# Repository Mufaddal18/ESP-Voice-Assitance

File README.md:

# ESP-Voice-Assitance

🚀 Excited to share my latest project: a fully integrated PCB for a voice assistant inspired by Avi Patel’s Gemini Voice Assistant!

This innovative design utilizes the Deepgram API for seamless speech-to-text conversion and leverages the Gemini API for intelligent responses, all while harnessing Google Text-to-Speech for natural-sounding replies.

🔑 Key Features:

1. Integrated Components: Powered by the ESP32, featuring a USB to TTL circuit, I2S microphone, and robust amplifier for top-notch performance.

2. Speech-to-Text Conversion: Impressively quick response time with Deepgram API.

3. Smart Audio Switching: Automatically toggles between speaker and earphone output for a personalized listening experience.

4. WAV File Storage: Efficiently processes longer questions by storing them as WAV files on an SD card.

5. Replay Functionality: A dedicated button to replay the last response, enhancing user interaction.

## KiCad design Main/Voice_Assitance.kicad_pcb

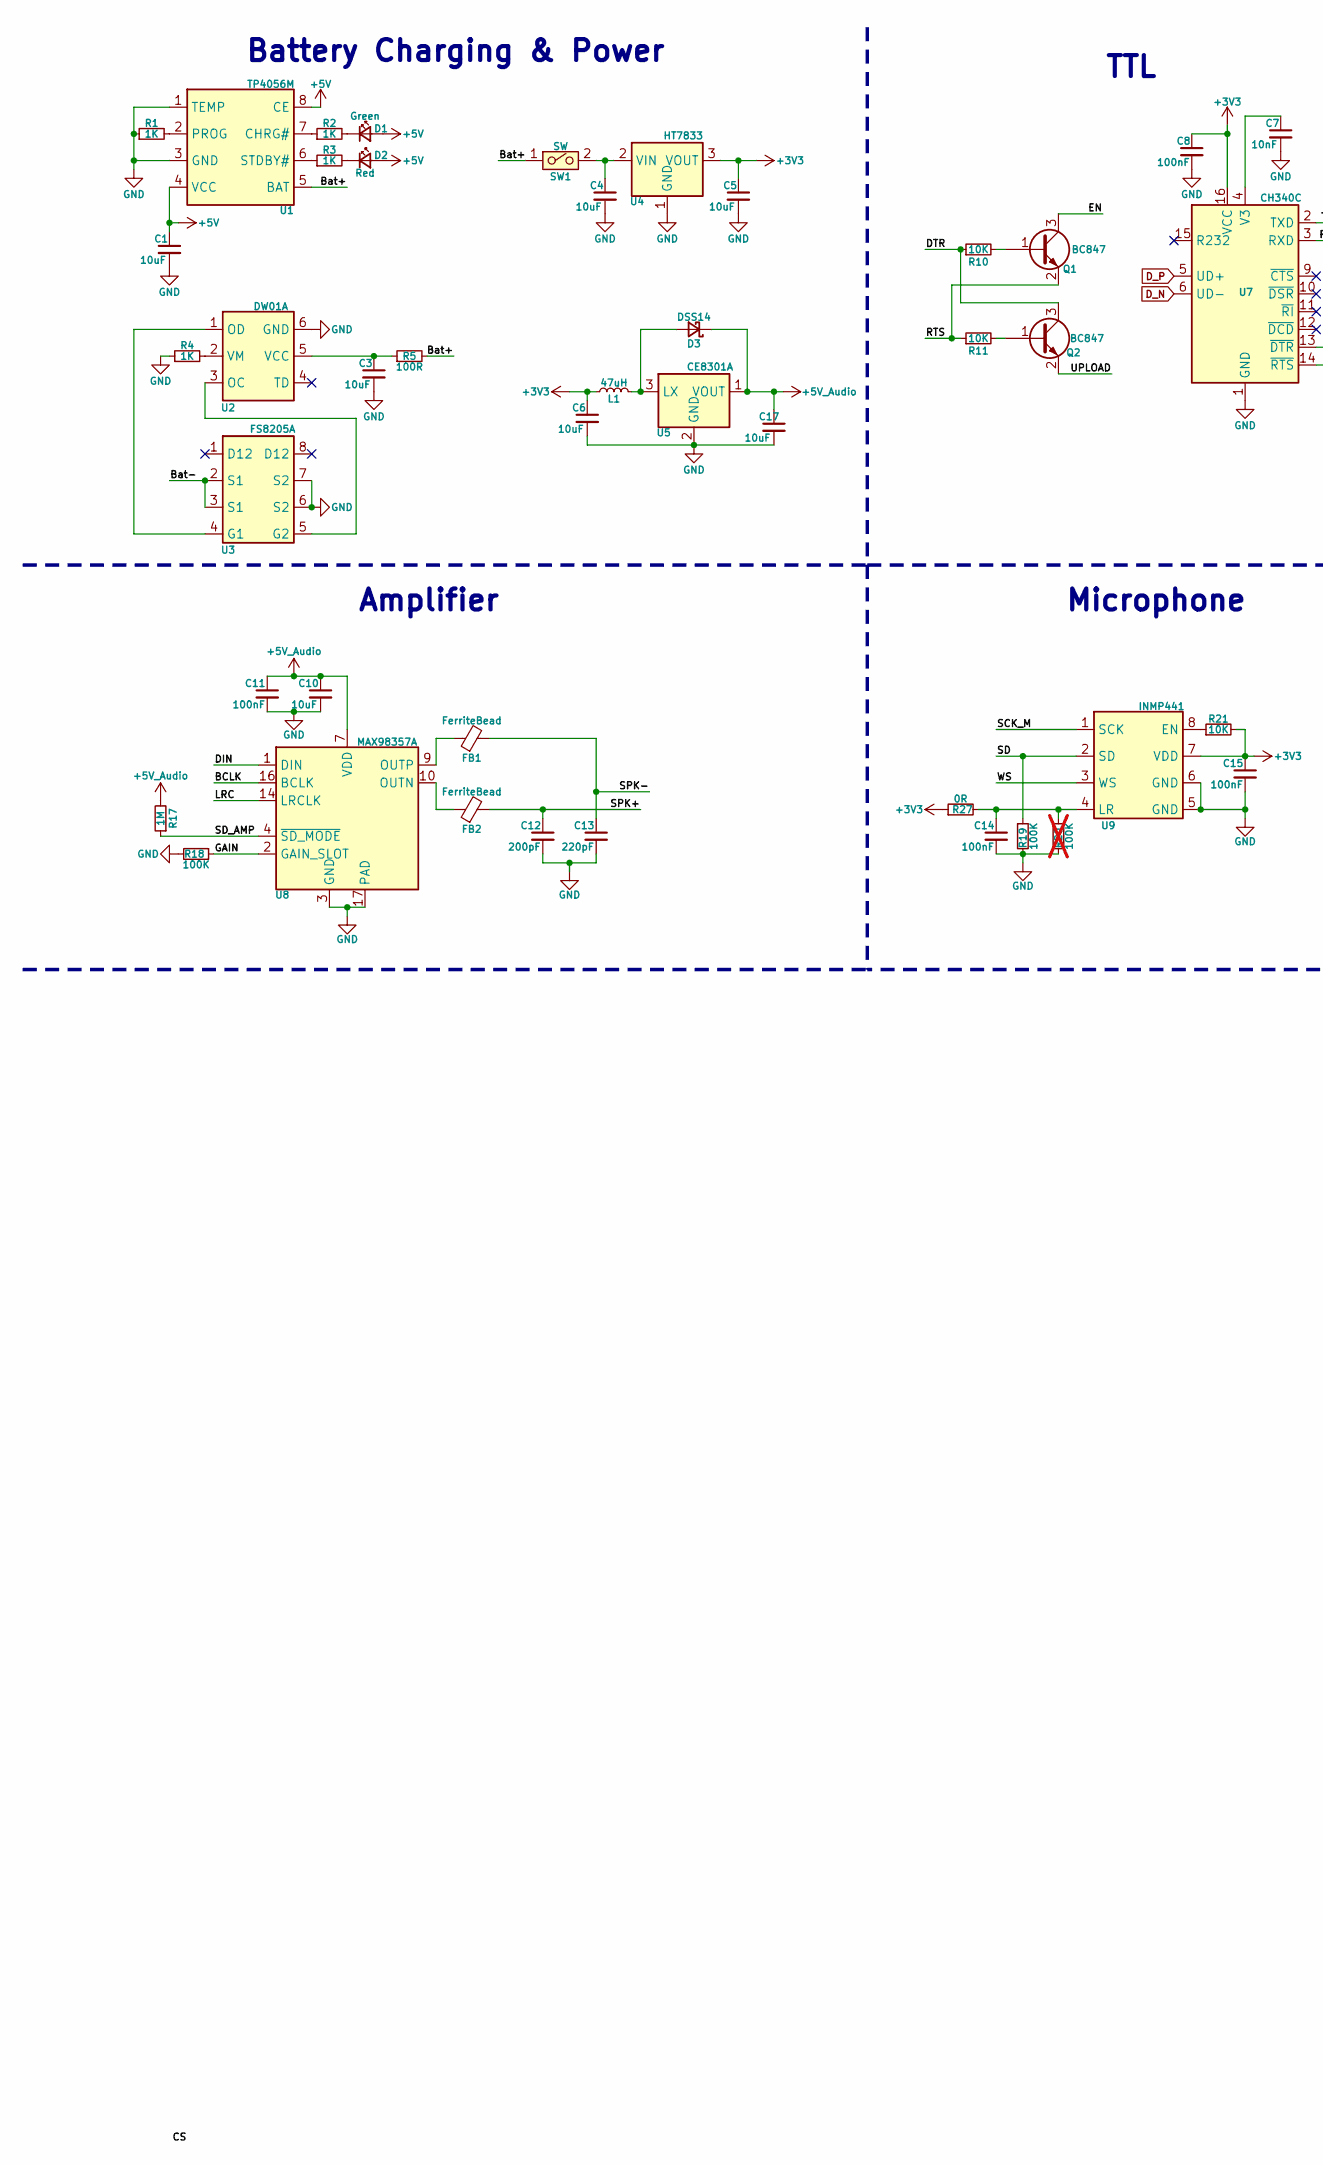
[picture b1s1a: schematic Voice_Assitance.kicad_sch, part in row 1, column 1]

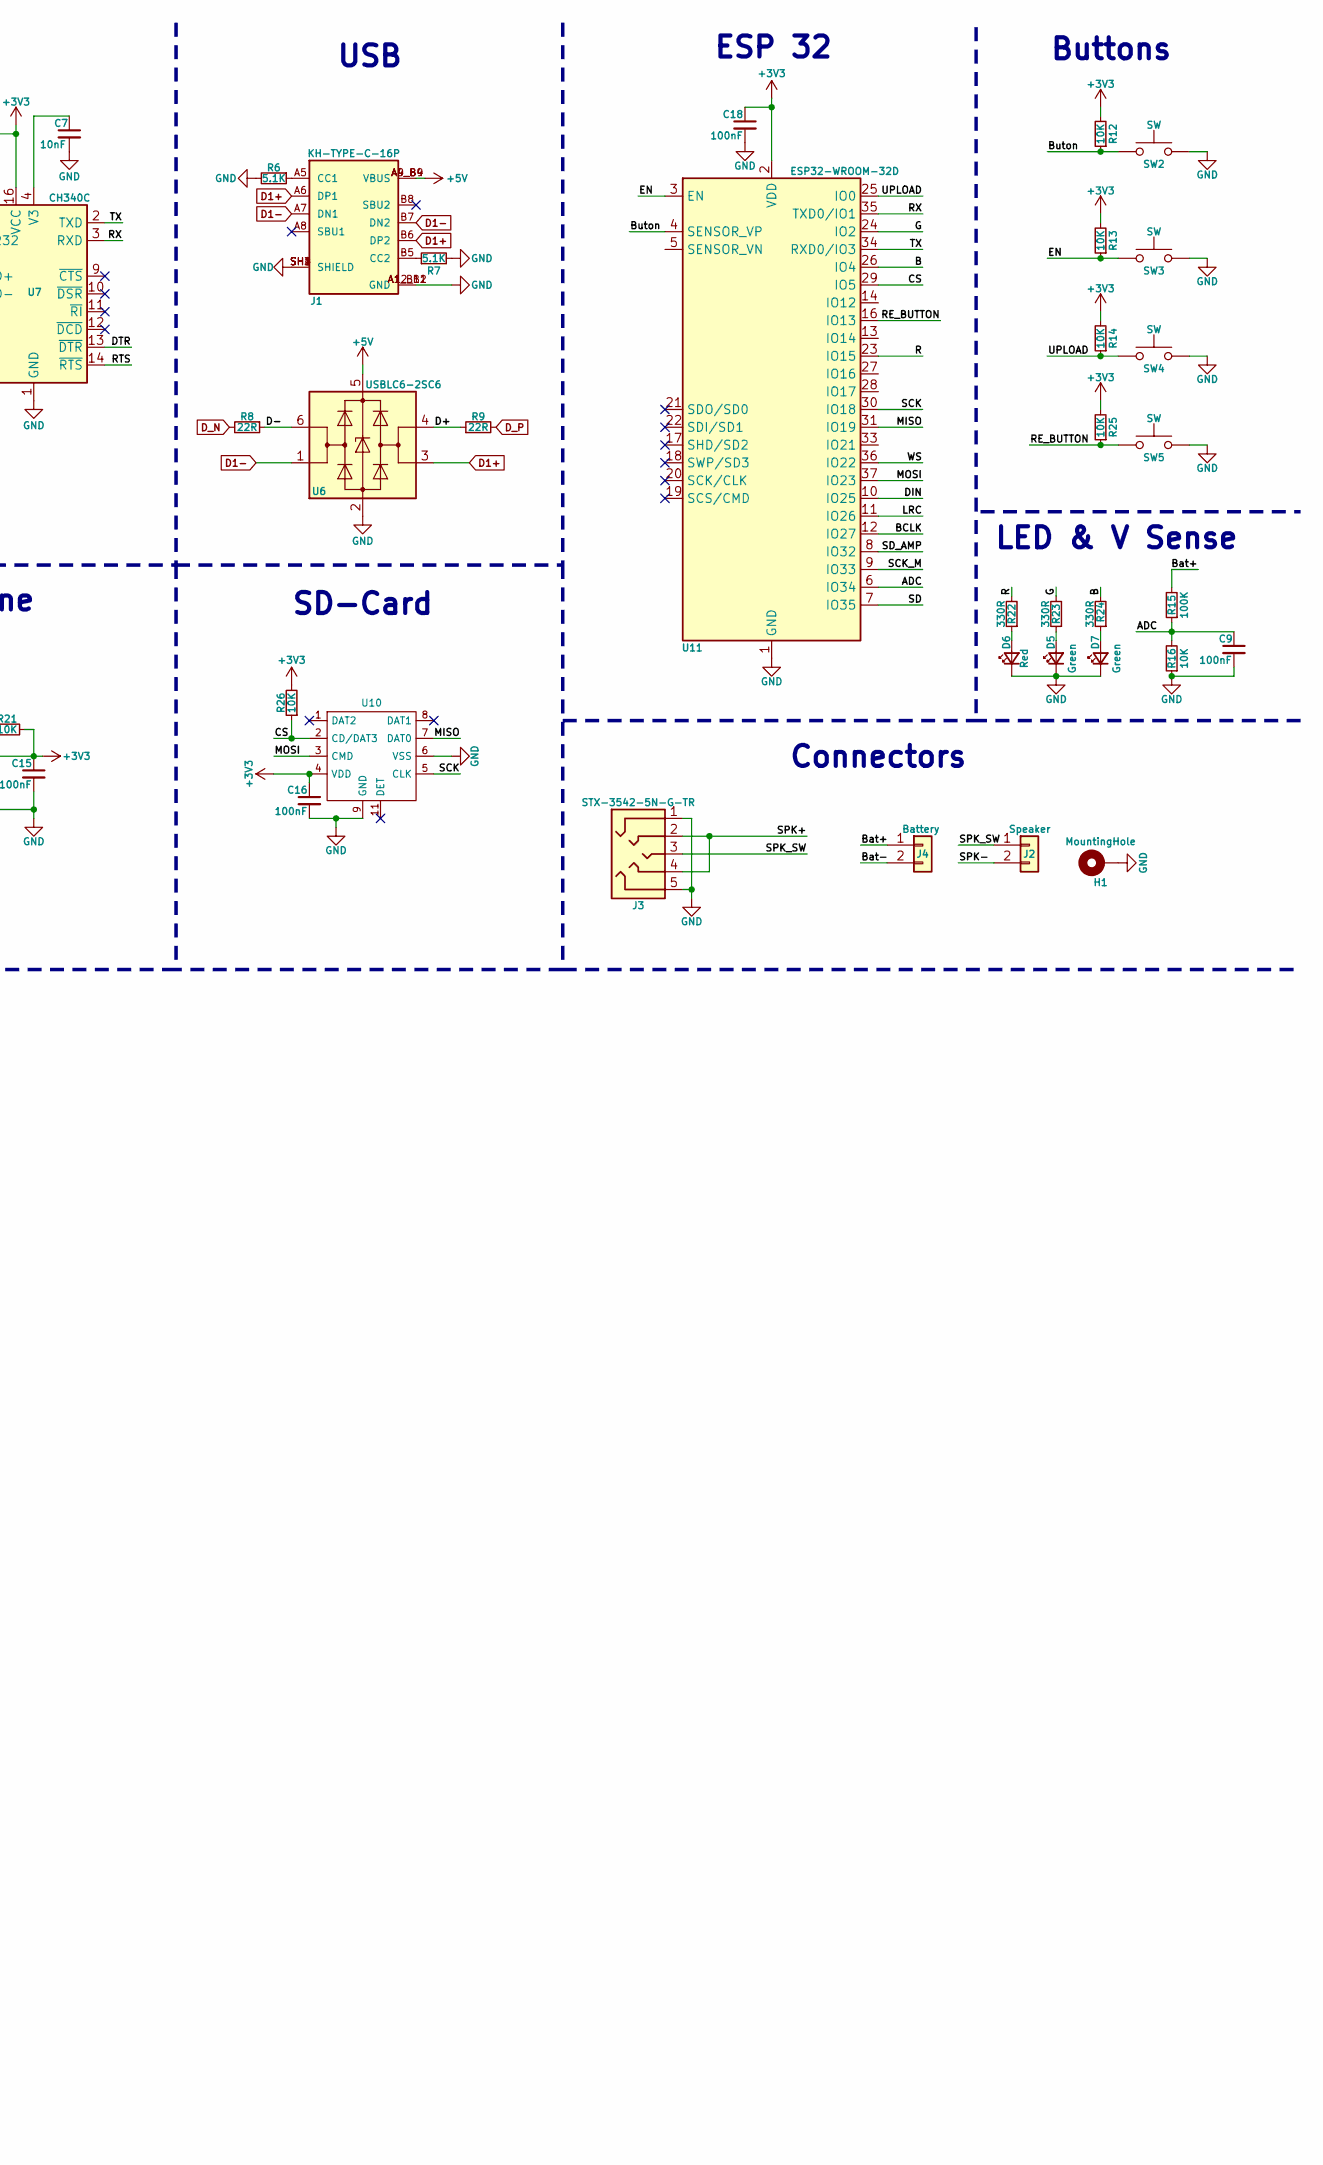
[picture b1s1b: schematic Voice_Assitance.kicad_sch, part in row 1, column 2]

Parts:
C1, C4, C5, C6: 10uF; C_0603_1608Metric_Pad1.08x0.95mm_HandSolder
C3, C10: 10uF; C_0402_1005Metric_Pad0.74x0.62mm_HandSolder
C7: 10nF; C_0402_1005Metric_Pad0.74x0.62mm_HandSolder
C8, C9, C11, C14, C15, C16: 100nF; C_0402_1005Metric_Pad0.74x0.62mm_HandSolder
C12: 200pF; C_0402_1005Metric_Pad0.74x0.62mm_HandSolder
C13: 220pF; C_0402_1005Metric_Pad0.74x0.62mm_HandSolder
C17: 10uF; C_0603_1608Metric
C18: 100nF; C_0603_1608Metric_Pad1.08x0.95mm_HandSolder
D1, D5, D7: Green; LED_0603_1608Metric_Pad1.05x0.95mm_HandSolder
D2, D6: Red; LED_0603_1608Metric_Pad1.05x0.95mm_HandSolder
D3: DSS14; D_SOD-123
FB1, FB2: FerriteBead; L_0402_1005Metric_Pad0.77x0.64mm_HandSolder
H1: MountingHole; MountingHole_4.3mm_M4_Pad
J1: KH-TYPE-C-16P; KINGHELM_KH-TYPE-C-16P
J2: Speaker; PinHeader_1x02_P2.00mm_Vertical
J3: STX-3542-5N-G-TR
J4: Battery; PinHeader_1x02_P2.00mm_Vertical
L1: 47uH; L_0402_1005Metric_Pad0.77x0.64mm_HandSolder
Q1, Q2: BC847; SOT-23
R1, R2, R3, R4: 1K; R_0402_1005Metric_Pad0.72x0.64mm_HandSolder
R5: 100R; R_0402_1005Metric_Pad0.72x0.64mm_HandSolder
R6, R7: 5.1K; R_0402_1005Metric_Pad0.72x0.64mm_HandSolder
R8, R9: 22R; R_0402_1005Metric_Pad0.72x0.64mm_HandSolder
R10, R11, R12, R13, R14, R16, R21, R25, R26: 10K; R_0402_1005Metric_Pad0.72x0.64mm_HandSolder
R15, R18, R19: 100K; R_0402_1005Metric_Pad0.72x0.64mm_HandSolder
R17: 1M; R_0402_1005Metric_Pad0.72x0.64mm_HandSolder
R20: 100K; R_0402_1005Metric_Pad0.72x0.64mm_HandSolder; not fitted
R22, R23, R24: 330R; R_0402_1005Metric_Pad0.72x0.64mm_HandSolder
R27: 0R; R_0402_1005Metric_Pad0.72x0.64mm_HandSolder
SW1: SW; MK-12C03-G015
SW2, SW3, SW4, SW5: SW; SW_TL3342F160QG_TR
U1: TP4056M; MSOP-8-1EP_3x3mm_P0.65mm_EP1.68x1.88mm
U2: DW01A; SOT-23-6
U3: FS8205A; TSSOP-8_4.4x3mm_P0.65mm
U4: HT7833; SOT-89-3
U5: CE8301A; SOT-23-3
U6: USBLC6-2SC6; SOT-23-6
U7: CH340C; SOP-16_3.9x9.9mm_P1.27mm
U8: MAX98357A; MAX98357AGTE_V+T
U9: INMP441
U10: 1040310811
U11: ESP32-WROOM-32D

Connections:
+3V3: C5.1, C6.1, C8.1, C15.1, C16.1, C18.1, L1.1, R12.2, R13.2, R14.2, R21.2, R25.2, R26.2, R27.1, U4.3 (VOUT), U7.16 (VCC), U9.7 (VDD), U10.4 (VDD), U11.2 (VDD)
+5V: C1.1, D1.2 (A), D2.2 (A), J1.A4_B9 (VBUS), J1.A9_B4 (VBUS), U1.4 (VCC), U1.8 (CE), U6.5 (VBUS)
+5V_Audio: C10.1, C11.1, C17.1, D3.1 (K), R17.2, U5.1 (VOUT), U8.7 (VDD), U8.8 (VDD)
/ADC: C9.1, R15.1, R16.2, U11.6 (IO34)
/B: R24.2, U11.26 (IO4)
/BCLK: U8.16 (BCLK), U11.12 (IO27)
/Bat+: J4.1, R5.2, R15.2, SW1.1, U1.5 (BAT)
/Bat-: J4.2, U3.2 (S1), U3.3 (S1)
/Buton: R12.1, SW2.1, U11.4 (SENSOR_VP)
/CS: R26.1, U10.2 (CD/DAT3), U11.29 (IO5)
/D+: R9.1, U6.4 (I/O2)
/D-: R8.1, U6.6 (I/O1)
/DIN: U8.1 (DIN), U11.10 (IO25)
/DTR: Q2.3 (C), R10.1, U7.13 (~DTR)
/EN: Q1.3 (C), R13.1, SW3.1, U11.3 (EN)
/G: R23.2, U11.24 (IO2)
/GAIN: R18.1, U8.2 (GAIN_SLOT)
/LRC: U8.14 (LRCLK), U11.11 (IO26)
/MISO: U10.7 (DAT0), U11.31 (IO19)
/MOSI: U10.3 (CMD), U11.37 (IO23)
/R: R22.2, U11.23 (IO15)
/RE_BUTTON: R25.1, SW5.1, U11.16 (IO13)
/RTS: Q1.2 (E), R11.1, U7.14 (~RTS)
/RX: U7.3 (RXD), U11.35 (TXD0/IO1)
/SCK: U10.5 (CLK), U11.30 (IO18)
/SCK_M: U9.1 (SCK), U11.9 (IO33)
/SD: R19.1, U9.2 (SD), U11.7 (IO35)
/SD_AMP: R17.1, U8.4 (~SD_MODE), U11.8 (IO32)
/SPK+: C12.1, FB2.2, J3.2, J3.4
/SPK-: C13.1, FB1.2, J2.2
/SPK_SW: J2.1, J3.3
/TX: U7.2 (TXD), U11.34 (RXD0/IO3)
/UPLOAD: Q2.2 (E), R14.1, SW4.1, U11.25 (IO0)
/WS: U9.3 (WS), U11.36 (IO22)
D1+: J1.A6 (DP1), J1.B6 (DP2), U6.3 (I/O2)
D1-: J1.A7 (DN1), J1.B7 (DN2), U6.1 (I/O1)
D_N: R8.2, U7.6 (UD-)
D_P: R9.2, U7.5 (UD+)
GND: C1.2, C3.2, C4.2, C5.2, C6.2, C7.2, C8.2, C9.2, C10.2, C11.2, C12.2, C13.2, C14.2, C15.2, C16.2, C17.2, C18.2, D5.1 (K), D6.1 (K), D7.1 (K), H1.1, J1.A1_B12 (GND), J1.A12_B1 (GND), J1.SH1 (SHIELD), J1.SH2 (SHIELD), J1.SH3 (SHIELD), J1.SH4 (SHIELD), J3.1, J3.5, R1.1, R4.1, R6.2, R7.2, R16.1, R18.2, R19.2, R20.2, SW2.2, SW3.2, SW4.2, SW5.2, U1.1 (TEMP), U1.3 (GND), U2.6 (GND), U3.6 (S2), U3.7 (S2), U4.1 (GND), U5.2 (GND), U6.2 (GND), U7.1 (GND), U8.3 (GND), U8.11 (GND), U8.15 (GND), U8.17 (PAD), U9.5 (GND), U9.6 (GND), U9.9 (GND), U10.6 (VSS), U10.9 (GND), U10.10 (GND), U10.12 (GND), U10.13 (GND), U10.14 (GND), U11.1 (GND), U11.15 (GND), U11.38 (GND), U11.39 (GND)
unnamed: D1.1 (K), R2.2
unnamed: D2.1 (K), R3.2
unnamed: D3.2 (A), L1.2, U5.3 (LX)
unnamed: D5.2 (A), R23.1
unnamed: D6.2 (A), R22.1
unnamed: D7.2 (A), R24.1
unnamed: J1.A5 (CC1), R6.1
unnamed: J1.B5 (CC2), R7.1
unnamed: Q1.1 (B), R10.2
unnamed: Q2.1 (B), R11.2
unnamed: R2.1, U1.7 (CHRG#)
unnamed: R1.2, U1.2 (PROG)
unnamed: R3.1, U1.6 (STDBY#)
unnamed: U2.3 (OC), U3.5 (G2)
unnamed: U2.1 (OD), U3.4 (G1)
unnamed: C3.1, R5.1, U2.5 (VCC)
unnamed: R4.2, U2.2 (VM)
unnamed: C4.1, SW1.2, U4.2 (VIN)
unnamed: C7.1, U7.4 (V3)
unnamed: FB2.1, U8.10 (OUTN)
unnamed: FB1.1, U8.9 (OUTP)
unnamed: R21.1, U9.8 (EN)
unnamed: C14.1, R20.1, R27.2, U9.4 (LR)

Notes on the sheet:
TTL
Amplifier
Connectors
SD-Card
Microphone
ESP 32
Battery Charging & Power
Buttons
USB
LED & V Sense

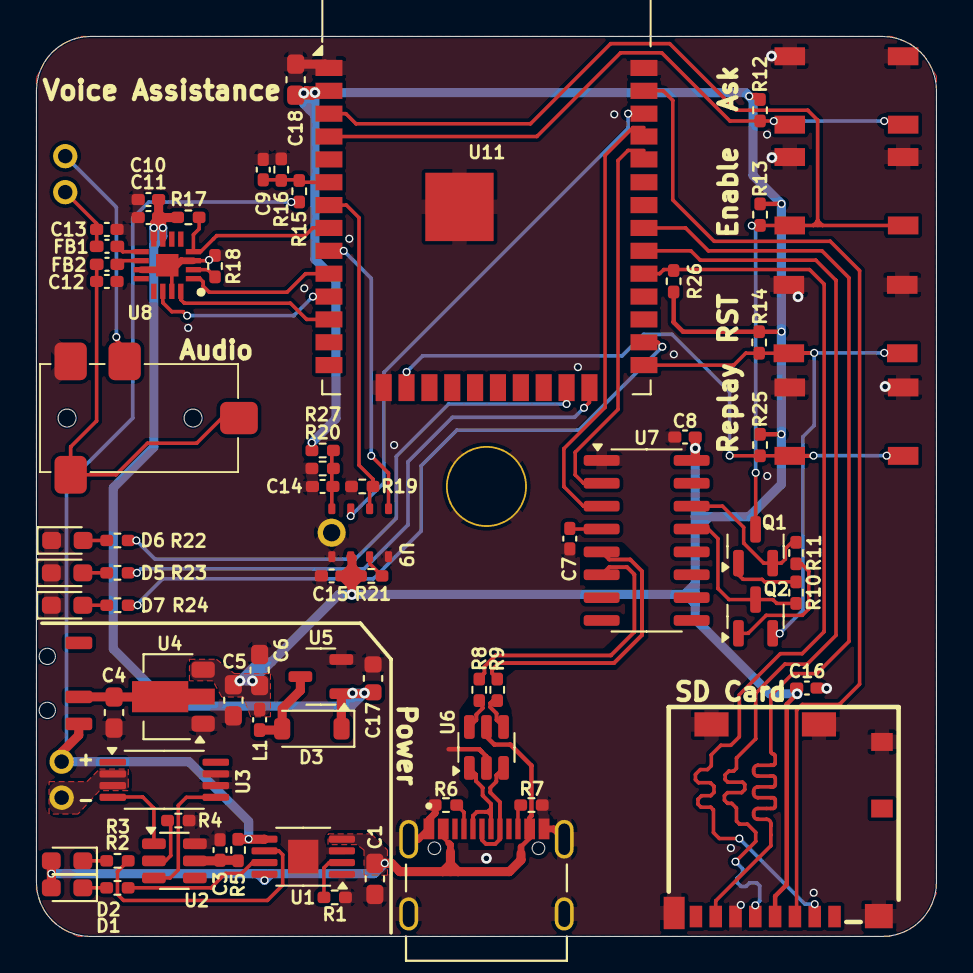
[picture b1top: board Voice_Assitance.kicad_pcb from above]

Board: 4 copper layers, 50.0 x 50.0 mm, 76 parts (0 on the bottom side), 62 nets.

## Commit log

2024-09-20 Create Read Me
